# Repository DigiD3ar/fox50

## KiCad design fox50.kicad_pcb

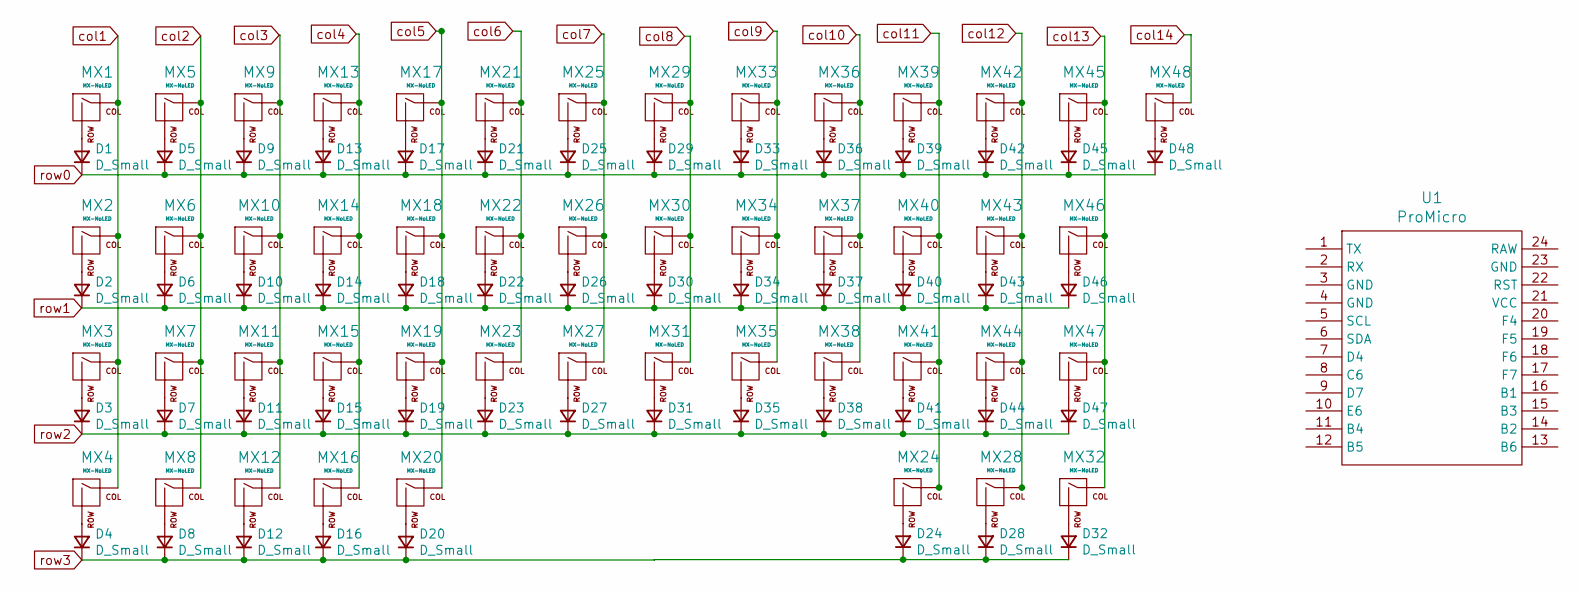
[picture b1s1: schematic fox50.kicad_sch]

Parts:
D1, D2, D3, D4, D5, D6, D7, D8, D9, D10, D11, D12, D13, D14, D15, D16, D17, D18, D19, D20, D21, D22, D23, D24, D25, D26, D27, D28, D29, D30, D31, D32, D33, D34, D35, D36, D37, D38, D39, D40, D41, D42, D43, D44, D45, D46, D47: D_Small; D_1206
D48: D_Small; SW_Cherry_MX_1.00u_PCB
MX1, MX2, MX3, MX4, MX5, MX6, MX7, MX8, MX9, MX10, MX11, MX12, MX13, MX14, MX15, MX16, MX17, MX18, MX19, MX20, MX21, MX22, MX23, MX24, MX25, MX26, MX27, MX28, MX29, MX30, MX31, MX32, MX33, MX34, MX35, MX36, MX37, MX38, MX39, MX40, MX41, MX42, MX43, MX44, MX45, MX46, MX47, MX48: MX-NoLED; SW_Cherry_MX_1.00u_PCB
U1: ProMicro; Pro_Micro

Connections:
unnamed: D1.2 (A), MX1.2 (ROW)
unnamed: D2.2 (A), MX2.2 (ROW)
unnamed: D3.2 (A), MX3.2 (ROW)
unnamed: D4.2 (A), MX4.2 (ROW)
unnamed: D5.2 (A), MX5.2 (ROW)
unnamed: D6.2 (A), MX6.2 (ROW)
unnamed: D7.2 (A), MX7.2 (ROW)
unnamed: D8.2 (A), MX8.2 (ROW)
unnamed: D9.2 (A), MX9.2 (ROW)
unnamed: D2.1 (K), D6.1 (K), D10.1 (K), D14.1 (K), D18.1 (K), D22.1 (K), D26.1 (K), D30.1 (K), D34.1 (K), D37.1 (K), D40.1 (K), D43.1 (K), D46.1 (K)
unnamed: D10.2 (A), MX10.2 (ROW)
unnamed: D11.2 (A), MX11.2 (ROW)
unnamed: D12.2 (A), MX12.2 (ROW)
unnamed: D13.2 (A), MX13.2 (ROW)
unnamed: D14.2 (A), MX14.2 (ROW)
unnamed: D15.2 (A), MX15.2 (ROW)
unnamed: D16.2 (A), MX16.2 (ROW)
unnamed: D17.2 (A), MX17.2 (ROW)
unnamed: D18.2 (A), MX18.2 (ROW)
unnamed: D19.2 (A), MX19.2 (ROW)
unnamed: D20.2 (A), MX20.2 (ROW)
unnamed: D21.2 (A), MX21.2 (ROW)
unnamed: D22.2 (A), MX22.2 (ROW)
unnamed: D23.2 (A), MX23.2 (ROW)
unnamed: D24.2 (A), MX24.2 (ROW)
unnamed: D25.2 (A), MX25.2 (ROW)
unnamed: D26.2 (A), MX26.2 (ROW)
unnamed: D27.2 (A), MX27.2 (ROW)
unnamed: D28.2 (A), MX28.2 (ROW)
unnamed: D29.2 (A), MX29.2 (ROW)
unnamed: D30.2 (A), MX30.2 (ROW)
unnamed: D31.2 (A), MX31.2 (ROW)
unnamed: D32.2 (A), MX32.2 (ROW)
unnamed: D33.2 (A), MX33.2 (ROW)
unnamed: D34.2 (A), MX34.2 (ROW)
unnamed: D35.2 (A), MX35.2 (ROW)
unnamed: D36.2 (A), MX36.2 (ROW)
unnamed: D37.2 (A), MX37.2 (ROW)
unnamed: D38.2 (A), MX38.2 (ROW)
unnamed: D39.2 (A), MX39.2 (ROW)
unnamed: D40.2 (A), MX40.2 (ROW)
unnamed: D41.2 (A), MX41.2 (ROW)
unnamed: D42.2 (A), MX42.2 (ROW)
unnamed: D43.2 (A), MX43.2 (ROW)
unnamed: D44.2 (A), MX44.2 (ROW)
unnamed: D45.2 (A), MX45.2 (ROW)
unnamed: D46.2 (A), MX46.2 (ROW)
unnamed: D47.2 (A), MX47.2 (ROW)
unnamed: D48.2 (A), MX48.2 (ROW)
col1: MX1.1 (COL), MX2.1 (COL), MX3.1 (COL), MX4.1 (COL)
col2: MX5.1 (COL), MX6.1 (COL), MX7.1 (COL), MX8.1 (COL)
col3: MX9.1 (COL), MX10.1 (COL), MX11.1 (COL), MX12.1 (COL)
col4: MX13.1 (COL), MX14.1 (COL), MX15.1 (COL), MX16.1 (COL)
col5: MX17.1 (COL), MX18.1 (COL), MX19.1 (COL), MX20.1 (COL)
col6: MX21.1 (COL), MX22.1 (COL), MX23.1 (COL)
col7: MX25.1 (COL), MX26.1 (COL), MX27.1 (COL)
col8: MX29.1 (COL), MX30.1 (COL), MX31.1 (COL)
col9: MX33.1 (COL), MX34.1 (COL), MX35.1 (COL)
col10: MX36.1 (COL), MX37.1 (COL), MX38.1 (COL)
col11: MX24.1 (COL), MX39.1 (COL), MX40.1 (COL), MX41.1 (COL)
col12: MX28.1 (COL), MX42.1 (COL), MX43.1 (COL), MX44.1 (COL)
col13: MX32.1 (COL), MX45.1 (COL), MX46.1 (COL), MX47.1 (COL)
col14: MX48.1 (COL)
row0: D1.1 (K), D5.1 (K), D9.1 (K), D13.1 (K), D17.1 (K), D21.1 (K), D25.1 (K), D29.1 (K), D33.1 (K), D36.1 (K), D39.1 (K), D42.1 (K), D45.1 (K), D48.1 (K)
row2: D3.1 (K), D7.1 (K), D11.1 (K), D15.1 (K), D19.1 (K), D23.1 (K), D27.1 (K), D31.1 (K), D35.1 (K), D38.1 (K), D41.1 (K), D44.1 (K), D47.1 (K)
row3: D4.1 (K), D8.1 (K), D12.1 (K), D16.1 (K), D20.1 (K), D24.1 (K), D28.1 (K), D32.1 (K)

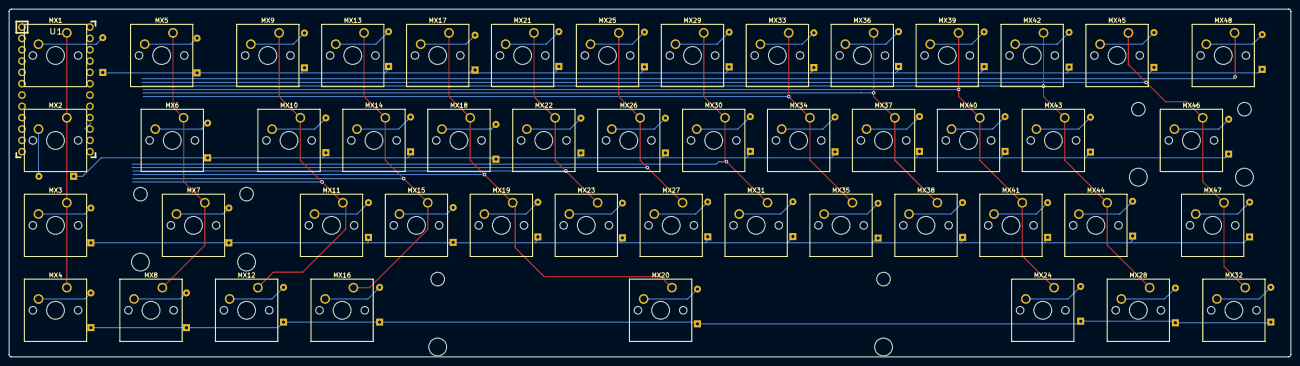
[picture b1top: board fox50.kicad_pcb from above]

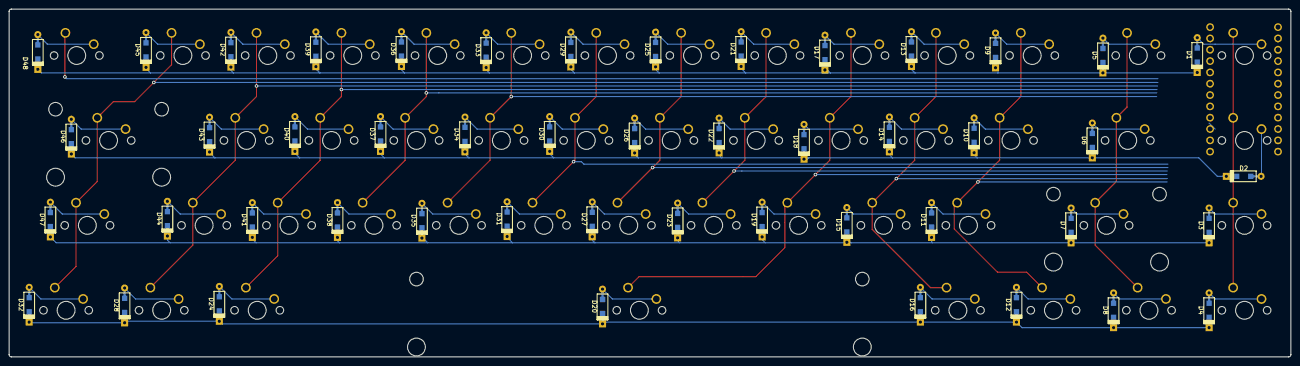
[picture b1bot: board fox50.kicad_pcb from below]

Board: 2 copper layers, 287.5 x 78.0 mm, 97 parts (48 on the bottom side), 65 nets.

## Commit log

2020-07-30 platilla de proyecto
2020-07-30 simbolos
2020-07-30 conexiones del eschema
2020-07-30 cols and rows
2020-07-30 smd done
2020-07-30 fix nets
2020-07-30 nets done 2
2020-07-30 red net done
2020-07-30 border done
2020-07-30 micro pos
2020-07-30 jefe final
